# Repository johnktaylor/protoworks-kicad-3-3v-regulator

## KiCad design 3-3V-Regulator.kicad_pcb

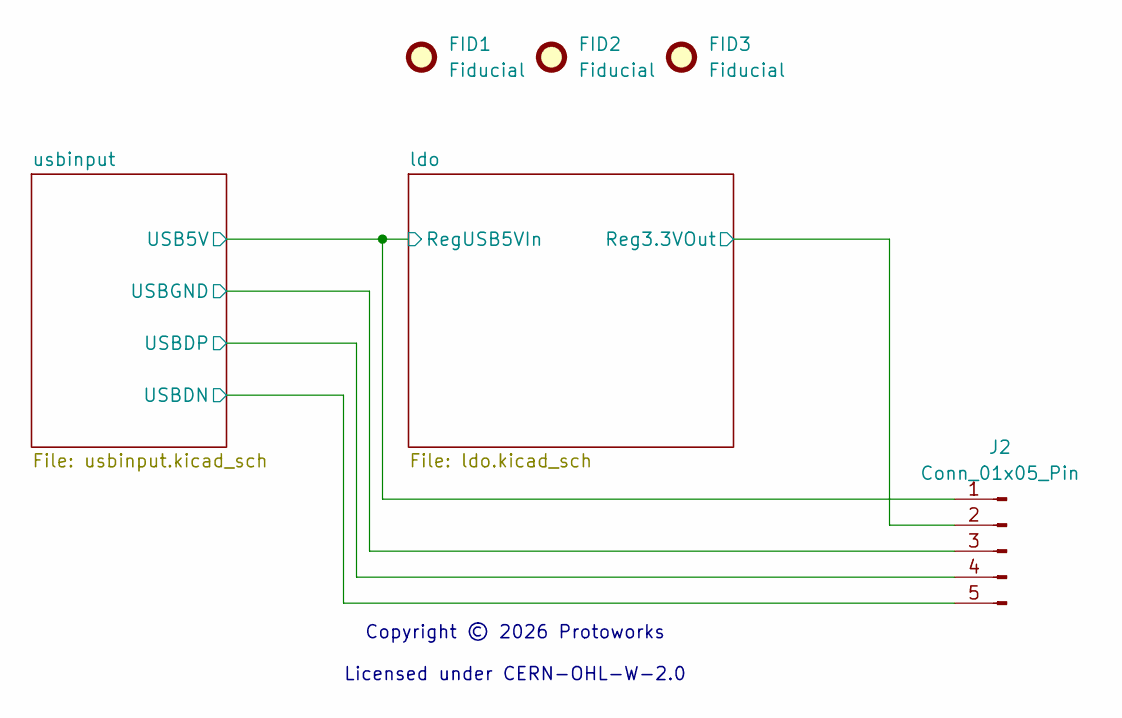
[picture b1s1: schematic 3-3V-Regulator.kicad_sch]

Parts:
FID1, FID2, FID3: Fiducial; Fiducial_0.75mm_Mask1.5mm
J2: Conn_01x05_Pin; PinHeader_1x05_P2.54mm_Vertical

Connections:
/ldo/Reg3.3VOut: J2.2; also elsewhere on the board
/ldo/RegUSB5VIn: J2.1; also elsewhere on the board
GND: J2.3; also elsewhere on the board
USBDN1: J2.5; also elsewhere on the board
USBDP1: J2.4; also elsewhere on the board

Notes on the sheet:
Copyright © 2026 Protoworks Licensed under CERN-OHL-W-2.0

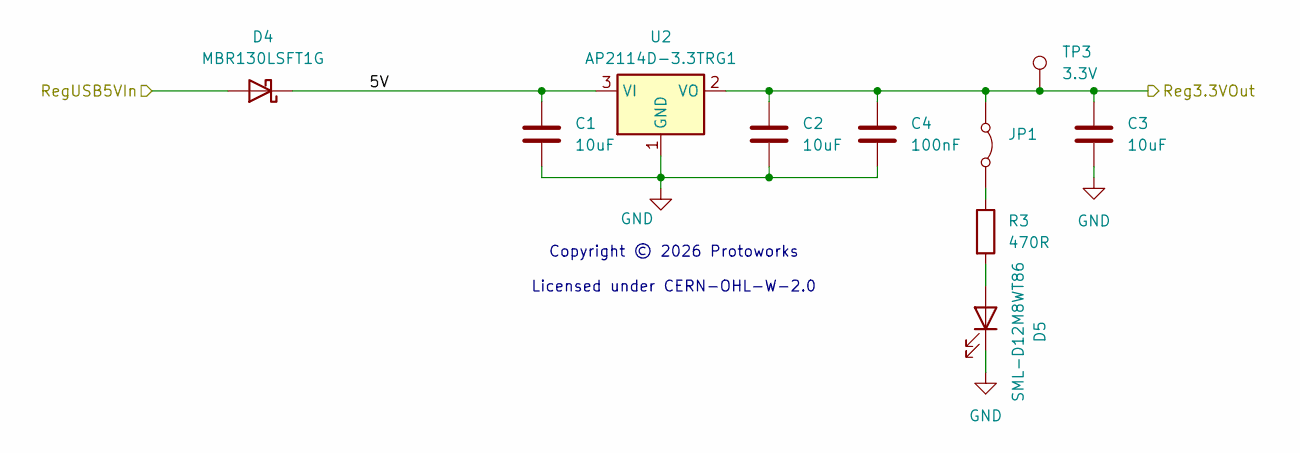
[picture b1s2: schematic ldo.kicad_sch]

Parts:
C1, C2, C3: 10uF; C_0805_2012Metric
C4: 100nF; C_0805_2012Metric
D4: MBR130LSFT1G; D_SOD-123
D5: SML-D12M8WT86; LED_0603_1608Metric_Pad1.05x0.95mm_HandSolder
JP1: Jumper_2_Bridged; SolderJumper-2_P1.3mm_Bridged_RoundedPad1.0x1.5mm
R3: 470R; R_0603_1608Metric_Pad0.98x0.95mm_HandSolder
TP3: 3.3V; TestPoint_Pad_1.0x1.0mm
U2: AP2114D-3.3TRG1; TO-252-3_TabPin2

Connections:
/ldo/5V: C1.1, D4.1 (K), U2.3 (VI)
/ldo/Reg3.3VOut: C2.1, C3.1, C4.1, JP1.1 (A), TP3.1 (1_1), U2.2 (VO); also elsewhere on the board
/ldo/RegUSB5VIn: D4.2 (A); also elsewhere on the board
GND: C1.2, C2.2, C3.2, C4.2, D5.1 (K), U2.1 (GND); also elsewhere on the board
unnamed: D5.2 (A), R3.2
unnamed: JP1.2 (B), R3.1

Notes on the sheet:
Copyright © 2026 Protoworks Licensed under CERN-OHL-W-2.0

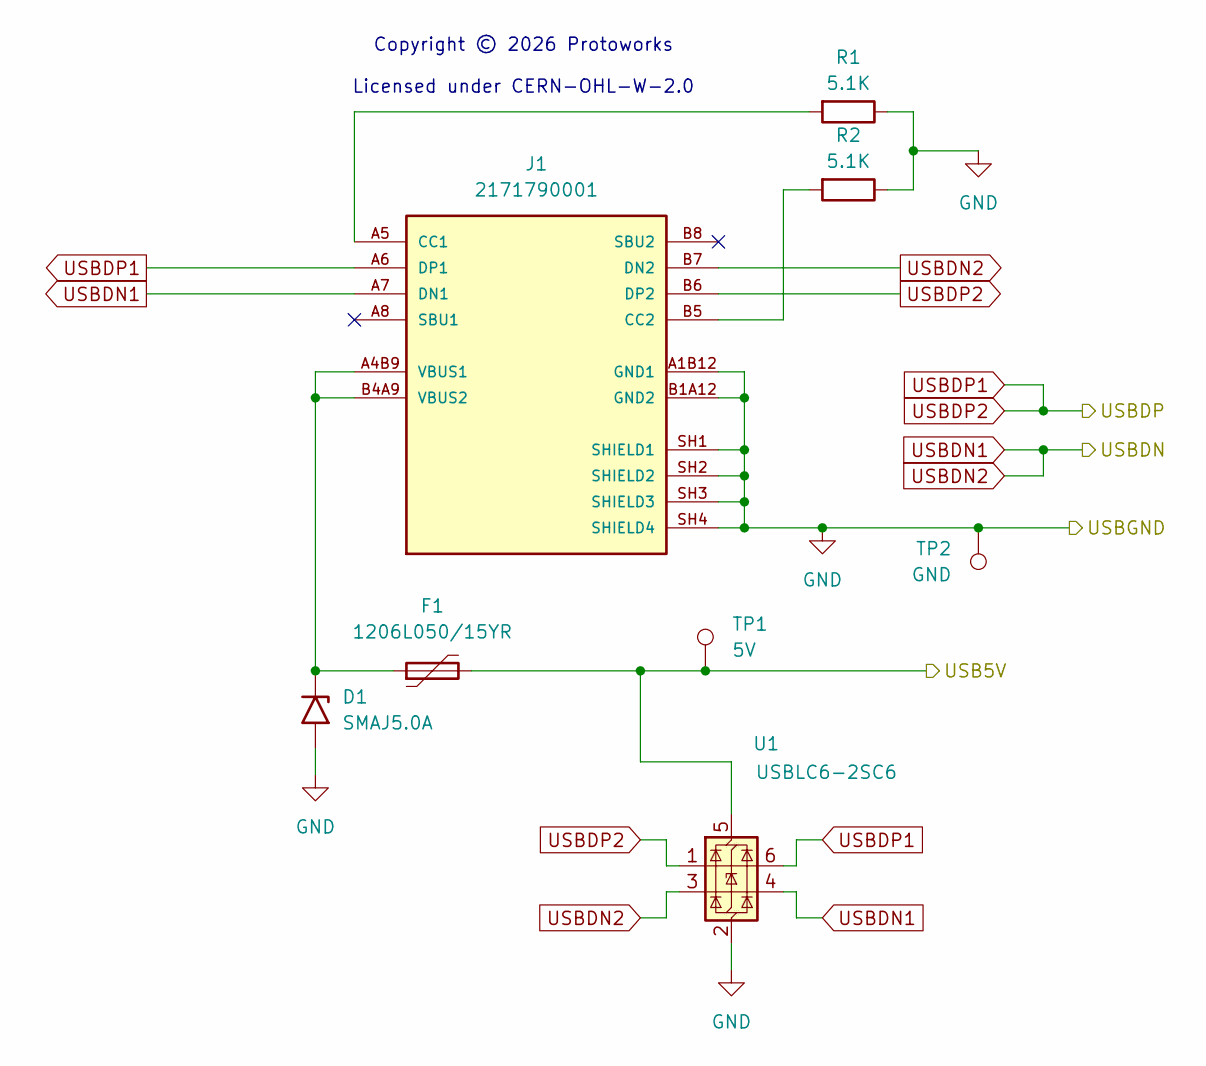
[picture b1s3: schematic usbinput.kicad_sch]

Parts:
D1: SMAJ5.0A; D_SMA
F1: 1206L050/15YR; Fuse_1206_3216Metric_Pad1.42x1.75mm_HandSolder
J1: 2171790001; MOLEX_2171790001; PARTREV A1
R1, R2: 5.1K; R_0603_1608Metric_Pad0.98x0.95mm_HandSolder
TP1: 5V; TestPoint_Pad_1.0x1.0mm
TP2: GND; TestPoint_Pad_1.0x1.0mm
U1: USBLC6-2SC6; SOT-23-6

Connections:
/ldo/RegUSB5VIn: F1.2, TP1.1 (1_1), U1.5 (VBUS); also elsewhere on the board
GND: D1.2 (A2), J1.A1B12 (GND1), J1.B1A12 (GND2), J1.SH1 (SHIELD1), J1.SH2 (SHIELD2), J1.SH3 (SHIELD3), J1.SH4 (SHIELD4), R1.1, R2.1, TP2.1 (1_1), U1.2 (GND); also elsewhere on the board
unnamed: D1.1 (A1), F1.1, J1.A4B9 (VBUS1), J1.B4A9 (VBUS2)
unnamed: J1.A5 (CC1), R1.2
unnamed: J1.B5 (CC2), R2.2
USBDN1: J1.A7 (DN1), J1.B7 (DN2), U1.3 (I/O2), U1.4 (I/O2); also elsewhere on the board
USBDP1: J1.A6 (DP1), J1.B6 (DP2), U1.1 (I/O1), U1.6 (I/O1); also elsewhere on the board

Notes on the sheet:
Copyright © 2026 Protoworks Licensed under CERN-OHL-W-2.0

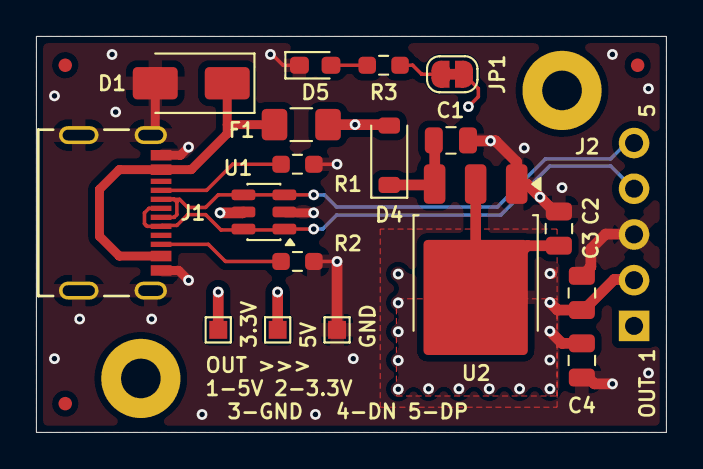
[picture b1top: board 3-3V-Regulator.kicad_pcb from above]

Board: 4 copper layers, 35.0 x 22.0 mm, 22 parts (1 on the bottom side), 11 nets.

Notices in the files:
3-3V-Regulator.kicad_pcb:
Copyright © 2026 Protoworks (NI)
